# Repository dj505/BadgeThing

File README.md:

# Untitled
A small homebrew dev board, previously known as BadgeThing

# What is it?
Untitled is a software-focused development board, and an excuse for me to learn a bit more about some specific hardware I'd like to incorporate into future projects. The main focus is the integrated SSD1306 OLED display, which I've used in earlier projects as a separate module. This time around, I wanted to adapt the circuit into the project itself to make the whole thing more cohesive.

I figured since it was going to have a screen, I needed to be able to use the screen for something, so I included hardware I was already familiar with to interface with. There's the RP2040 I've used in other previous projects, and I've played with the ESP8266 before in the context of Arduino-like programming, so I thought I would try integrating that into this design so I could play with the AT firmware a little. I've used WS2812B LEDs a ton and thought they'd make a good set of indicators. And, since I wanted this to be versatile, it features some screw holes as well as slits along either side to mount using a wrist strap or some type of band to attach to other things without screws. It could even be wearable!

Oh, and it's called "Untitled" because I couldn't think of a witty name for this one. I originally wanted to call it the "no name development board with rp2040 and esp8266" with a logo and black/yellow colour scheme that parody the Canadian "no name" brand, but JLC doesn't offer black silkscreen on yellow solder mask, so I had to change it up.

# Features
- Built-in SSD1306 128*64 OLED display driven over SPI
- Raspberry Pi RP2040
- ESP-12 module for WiFi
  - Compatible with ESP-12E, ESP-12F, and ESP-12S
- Piezo buzzer pins (though they can be repurposed for other parts that use 1 GPIO)
- Row of 4 addressable RGB LEDs
- 5 buttons for input and/or navigation
- Extra GPIO broken out, with access to additional SPI/UART/I2C busses if needed
- Wristband/wrist strap slots and mounting holes

# Custom SSD1306 footprint
I couldn't find an easy-to-place foorptint for the 30-pin SSD1306 display, so this project includes a custom KICAD footprint for the typical 12mm length/7mm pin pitch ribbon cable variant you can find for cheap on AliExpress. There are 4 variants, two meant for mounting the screen on the front of the board, and two for mounting it on the back. Both placements have variants including and excluding a cutout in the Edge.Cuts layer for the ribbon cable to pass through. **You are free to use these footprints in any project you want! I just ask that credit is provided.**

There is also a custom symbol in the schematic for the display, based off of Adafruit's schematic. I can't guarantee all the pins are labelled correctly. I have tested it, and it does work, but you should research and double check the correct pinouts for your own project.

If you end up using either of these, and found them useful, please consider sending a small tip my way!  

# Parts
The majority of the parts are clearly labelled in the schematic and/or come with LCSC part numbers available through JLC. Not all of them are basic parts, unfortunately, but I used as many as I possibly could. You're also free to order part like the ESP-12 module separately and solder it yourself to save on assembly costs. However, it's important to keep in mind the following:
- The OLED diplay is made with a **0.7mm pin pitch in mind.** Some of the displays available have a 0.5mm pin pitch and will not fit.
- The display's ribbon cable should be **no longer than ~12mm** otherwise it will not fit the footprint without extra slack.
- Every ESP-12 model should fit this footprint, however I use the ESP-12S due to it supposedly having the best antenna efficiency. The missing pins along the bottom of the footprint are OK because this design does not use them, and they only serve to provide extra mechanical strength.
- The RGB LEDs are made with WS2812B-V5 LEDs in mind specifically, as they have built-in capacitors and such that I was not able to reliably fit on the PCB. Other pin-compatible and signal-compatible LEDs will work, and there is a footprint for one large capacitor. In my testing, LEDs that don't have a built in capacitor worked fine without one, but there may be cases where this does not hold true. Check the datasheet for the LEDs you plan to use to make sure they do not require an external capacitor.

# Ordering for assembly
As this project is meant to be mainly for personal use, I won't go into extensive detail here on how to order this board for assembly. However, a pre-made gerber zip is included in the "production" directory, and the BOM/CPL files can be generated through KiCAD. I recommend using the JLCPCB export plugin to do the heavy lifting for you - the LCSC part numbers I used for most components should be included in the schematic. Feel free to poke me with questions over Discord! You can reach me @dj505.

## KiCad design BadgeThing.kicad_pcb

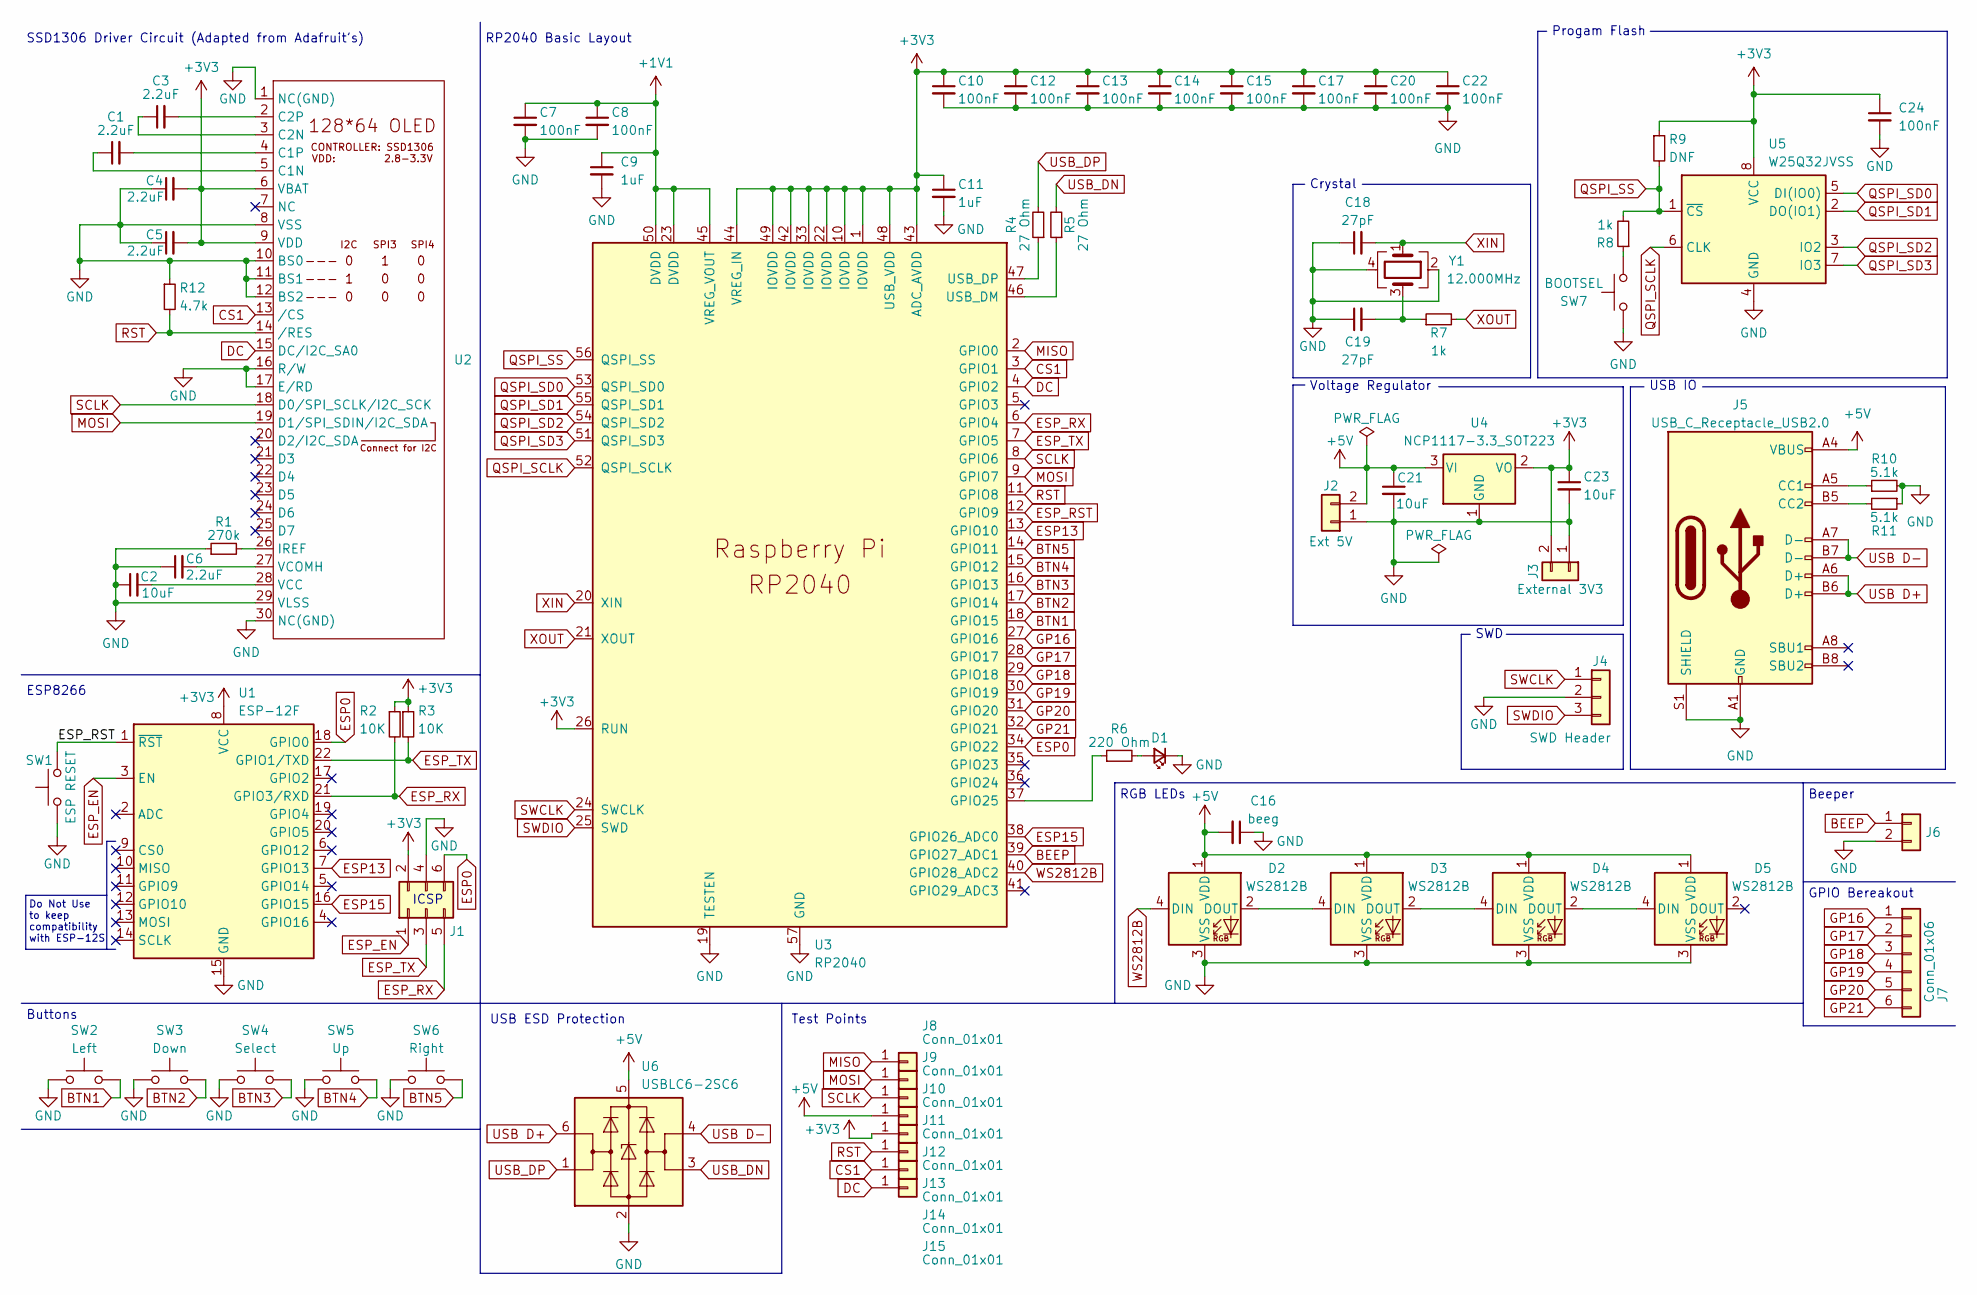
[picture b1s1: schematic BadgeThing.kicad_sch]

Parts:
C1, C3, C4, C5, C6: 2.2uF; C_0402_1005Metric_Pad0.74x0.62mm_HandSolder; LCSC C12530
C2, C21, C23: 10uF; C_0402_1005Metric_Pad0.74x0.62mm_HandSolder; LCSC C15525
C7, C8, C10, C12, C13, C14, C15, C17, C20, C22, C24: 100nF; C_0402_1005Metric_Pad0.74x0.62mm_HandSolder; LCSC C1525
C9, C11: 1uF; C_0402_1005Metric_Pad0.74x0.62mm_HandSolder; LCSC C52923
C16: beeg; C_0402_1005Metric_Pad0.74x0.62mm_HandSolder; LCSC C12530
C18, C19: 27pF; C_0402_1005Metric_Pad0.74x0.62mm_HandSolder; LCSC C1557
D1: DNF; LED_0805_2012Metric_Pad1.15x1.40mm_HandSolder; LCSC C2297
D2, D3, D4, D5: WS2812B; LED_WS2812B_PLCC4_5.0x5.0mm_P3.2mm; LCSC C2761795
J1: PinHeader_2x03_P2.54mm_Vertical
J2: Ext 5V; PinHeader_1x02_P2.54mm_Vertical
J3: External 3V3; PinHeader_1x02_P2.54mm_Vertical
J4: SWD Header; PinHeader_1x03_P1.27mm_Vertical
J5: USB_C_Receptacle_USB2.0; USB_C_Receptacle_G-Switch_GT-USB-7010ASV; LCSC C2988369
J6: Connector_Generic_Conn_01x02; PinHeader_1x02_P2.54mm_Vertical
J7: Conn_01x06; PinHeader_1x06_P2.00mm_Vertical
J8, J9, J10, J11, J12, J13, J14, J15: Conn_01x01; PinHeader_1x01_P2.00mm_Vertical
R1: 270k; R_0402_1005Metric_Pad0.72x0.64mm_HandSolder; LCSC C25770
R2, R3: 10K; R_0402_1005Metric_Pad0.72x0.64mm_HandSolder; LCSC C25744
R4, R5: 27 Ohm; R_0402_1005Metric_Pad0.72x0.64mm_HandSolder; LCSC C2909343
R6: 220 Ohm; R_0402_1005Metric_Pad0.72x0.64mm_HandSolder; LCSC C25091
R7, R8: 1k; R_0402_1005Metric_Pad0.72x0.64mm_HandSolder; LCSC C11702
R9: DNF; R_0402_1005Metric_Pad0.72x0.64mm_HandSolder; LCSC C25744
R10, R11: 5.1k; R_0402_1005Metric_Pad0.72x0.64mm_HandSolder; LCSC C25905
R12: 4.7k; R_0402_1005Metric_Pad0.72x0.64mm_HandSolder; LCSC C25900
SW1: ESP RESET; SW_Push_1P1T_XKB_TS-1187A; LCSC C318884
SW2: Left; SW_Push_1P1T_NO_6x6mm_H9.5mm
SW3: Down; SW_Push_1P1T_NO_6x6mm_H9.5mm
SW4: Select; SW_Push_1P1T_NO_6x6mm_H9.5mm
SW5: Up; SW_Push_1P1T_NO_6x6mm_H9.5mm
SW6: Right; SW_Push_1P1T_NO_6x6mm_H9.5mm
SW7: BOOTSEL; SW_Push_1P1T_XKB_TS-1187A; LCSC C318884
U1: ESP-12F; ESP-12E; LCSC C82898
U2: SSD1306 0.5mm Pitch
U3: RP2040; RP2040-QFN-56; LCSC C2040
U4: NCP1117-3.3_SOT223; SOT-223-3_TabPin2; LCSC C146799
U5: W25Q32JVSS; SOIC-8_5.23x5.23mm_P1.27mm; LCSC C82344
U6: USBLC6-2SC6; SOT-23-6; LCSC C2687116
Y1: 12.000MHz; Crystal_SMD_3225-4Pin_3.2x2.5mm; LCSC C9002

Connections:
+1V1: C7.1, C8.1, C9.1, U3.23 (DVDD), U3.45 (VREG_VOUT), U3.50 (DVDD)
+3V3: C4.2, C5.2, C10.1, C11.1, C12.1, C13.1, C14.1, C15.1, C17.1, C20.1, C22.1, C23.1, C24.1, J1.2, J3.2, J12.1, R2.1, R3.1, R9.1, U1.8 (VCC), U2.6 (VBAT), U2.9 (VDD), U3.1 (IOVDD), U3.10 (IOVDD), U3.22 (IOVDD), U3.26 (RUN), U3.33 (IOVDD), U3.42 (IOVDD), U3.43 (ADC_AVDD), U3.44 (VREG_IN), U3.48 (USB_VDD), U3.49 (IOVDD), U4.2 (VO), U5.8 (VCC)
+5V: C16.2, C21.1, D2.1 (VDD), D3.1 (VDD), D4.1 (VDD), D5.1 (VDD), J2.2, J5.A4 (VBUS), J5.A9 (VBUS), J5.B4 (VBUS), J5.B9 (VBUS), J11.1, U4.3 (VI), U6.5 (VBUS)
BEEP: J6.1, U3.39 (GPIO27_ADC1)
BTN1: SW2.2, U3.18 (GPIO15)
BTN2: SW3.2, U3.17 (GPIO14)
BTN3: SW4.2, U3.16 (GPIO13)
BTN4: SW5.2, U3.15 (GPIO12)
BTN5: SW6.2, U3.14 (GPIO11)
CS1: J14.1, U2.13 (/CS), U3.3 (GPIO1)
DC: J15.1, U2.15 (DC/I2C_SA0), U3.4 (GPIO2)
ESP0: J1.6, U1.18 (GPIO0), U3.34 (GPIO22)
ESP13: U1.7 (GPIO13), U3.13 (GPIO10)
ESP15: U1.16 (GPIO15), U3.38 (GPIO26_ADC0)
ESP_EN: J1.1, U1.3 (EN)
ESP_RST: SW1.2, U1.1 (~RST), U3.12 (GPIO9)
ESP_RX: J1.5, R2.2, U1.21 (GPIO3/RXD), U3.6 (GPIO4)
ESP_TX: J1.3, R3.2, U1.22 (GPIO1/TXD), U3.7 (GPIO5)
GND: C2.1, C4.1, C5.1, C6.1, C7.2, C8.2, C9.2, C10.2, C11.2, C12.2, C13.2, C14.2, C15.2, C16.1, C17.2, C18.1, C19.1, C20.2, C21.2, C22.2, C23.2, C24.2, D1.1 (K), D2.3 (VSS), D3.3 (VSS), D4.3 (VSS), D5.3 (VSS), J1.4, J2.1, J3.1, J4.2, J5.A1 (GND), J5.A12 (GND), J5.B1 (GND), J5.B12 (GND), J5.S1 (SHIELD), J6.2, R1.1, R10.2, R11.1, R12.1, SW1.1, SW2.1, SW3.1, SW4.1, SW5.1, SW6.1, SW7.1, U1.15 (GND), U2.1 (NC(GND)), U2.8 (VSS), U2.10 (BS0), U2.11 (BS1), U2.12 (BS2), U2.16 (R/W), U2.17 (E/RD), U2.29 (VLSS), U2.30 (NC(GND)), U3.19 (TESTEN), U3.57 (GND), U4.1 (GND), U5.4 (GND), U6.2 (GND), Y1.2, Y1.4
GP16: J7.1, U3.27 (GPIO16)
GP17: J7.2, U3.28 (GPIO17)
GP18: J7.3, U3.29 (GPIO18)
GP19: J7.4, U3.30 (GPIO19)
GP20: J7.5, U3.31 (GPIO20)
GP21: J7.6, U3.32 (GPIO21)
MISO: J8.1, U3.2 (GPIO0)
MOSI: J9.1, U2.19 (D1/SPI_SDIN/I2C_SDA), U3.9 (GPIO7)
unnamed: C19.2, R7.1, Y1.3
unnamed: D1.2 (A), R6.2
unnamed: D2.2 (DOUT), D3.4 (DIN)
unnamed: D3.2 (DOUT), D4.4 (DIN)
unnamed: D4.2 (DOUT), D5.4 (DIN)
unnamed: J5.A5 (CC1), R10.1
unnamed: J5.B5 (CC2), R11.2
unnamed: R8.1, SW7.2
unnamed: C1.1, U2.5 (C1N)
unnamed: C1.2, U2.4 (C1P)
unnamed: C3.1, U2.3 (C2N)
unnamed: C3.2, U2.2 (C2P)
unnamed: R1.2, U2.26 (IREF)
unnamed: C2.2, U2.28 (VCC)
unnamed: C6.2, U2.27 (VCOMH)
unnamed: R6.1, U3.37 (GPIO25)
unnamed: R5.1, U3.46 (USB_DM)
unnamed: R4.1, U3.47 (USB_DP)
QSPI_SCLK: U3.52 (QSPI_SCLK), U5.6 (CLK)
QSPI_SD0: U3.53 (QSPI_SD0), U5.5 (DI(IO0))
QSPI_SD1: U3.55 (QSPI_SD1), U5.2 (DO(IO1))
QSPI_SD2: U3.54 (QSPI_SD2), U5.3 (IO2)
QSPI_SD3: U3.51 (QSPI_SD3), U5.7 (IO3)
QSPI_SS: R8.2, R9.2, U3.56 (QSPI_SS), U5.1 (~CS)
RST: J13.1, R12.2, U2.14 (/RES), U3.11 (GPIO8)
SCLK: J10.1, U2.18 (D0/SPI_SCLK/I2C_SCK), U3.8 (GPIO6)
SWCLK: J4.1, U3.24 (SWCLK)
SWDIO: J4.3, U3.25 (SWD)
USB D+: J5.A6 (D+), J5.B6 (D+), U6.6 (I/O1)
USB D-: J5.A7 (D-), J5.B7 (D-), U6.4 (I/O2)
USB_DN: R5.2, U6.3 (I/O2)
USB_DP: R4.2, U6.1 (I/O1)
WS2812B: D2.4 (DIN), U3.40 (GPIO28_ADC2)
XIN: C18.2, U3.20 (XIN), Y1.1
XOUT: R7.2, U3.21 (XOUT)

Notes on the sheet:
Buttons
USB ESD Protection
RP2040 Basic Layout
SWD
SSD1306 Driver Circuit (Adapted from Adafruit's)
Do Not Use to keep compatibility with ESP-12S
Progam Flash
ESP8266
Beeper
ICSP
Crystal
RGB LEDs
USB IO
GPIO Bereakout
Test Points
Voltage Regulator

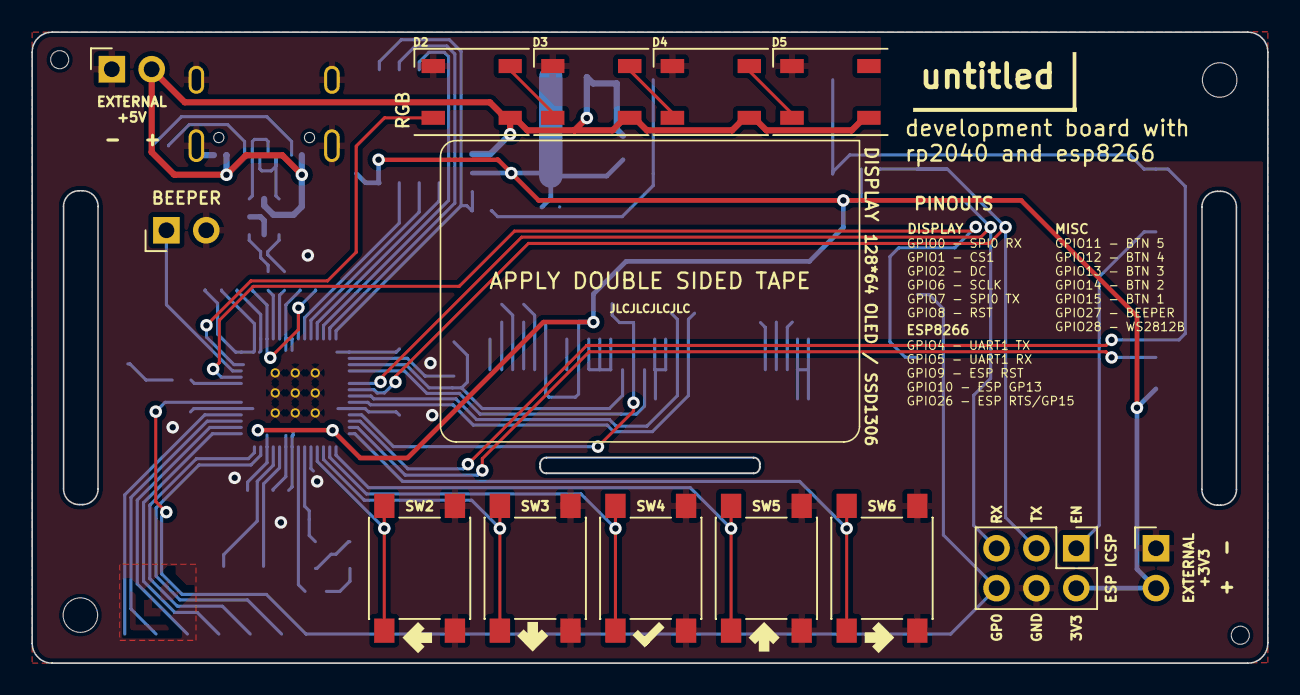
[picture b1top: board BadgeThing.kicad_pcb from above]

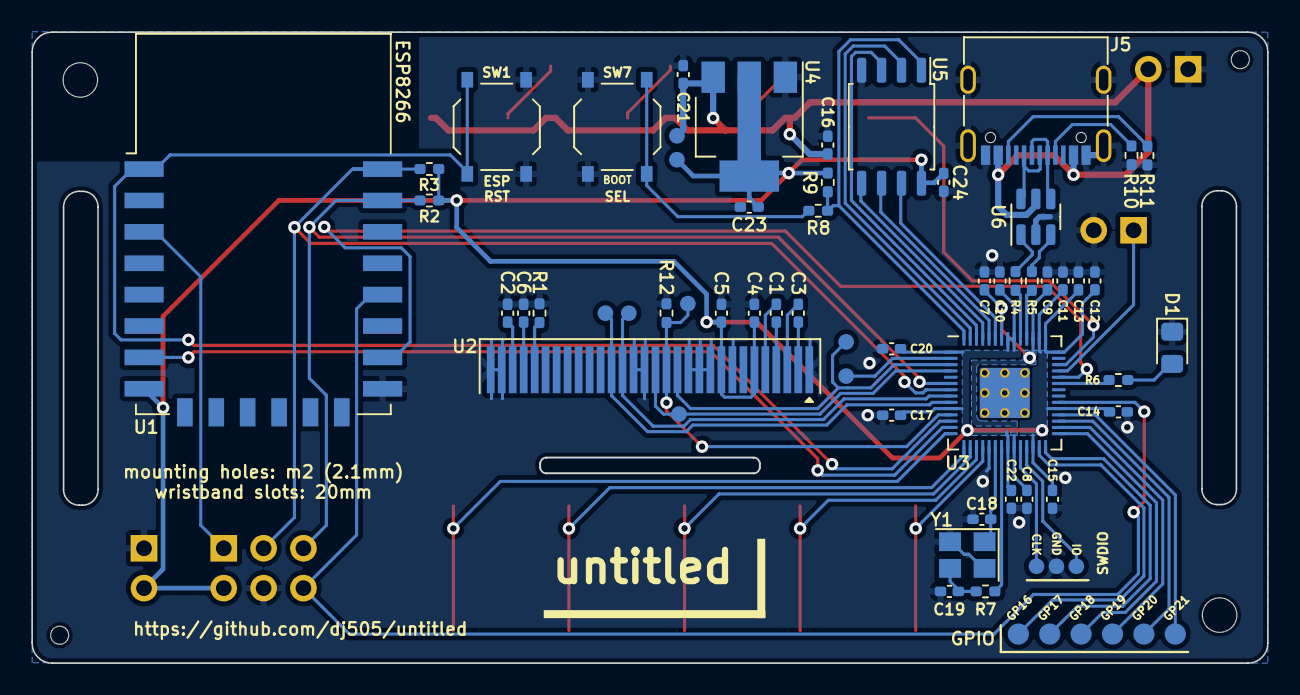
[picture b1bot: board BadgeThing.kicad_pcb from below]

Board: 2 copper layers, 78.7 x 40.2 mm, 70 parts (56 on the bottom side), 62 nets.

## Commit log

2024-01-09 Initial schematic
2024-01-12 RP2040/OLED circuits, basic component placement
2024-01-12 Schematic change
2024-01-12 more routing + layout
2024-01-12 Completed initial routing
2024-01-12 small tweaks, visual changes, added missing traces
2024-01-13 Layout tweaks + JLC part numbers
2024-01-14 Final board layout, up to first production order
2024-01-14 3V3 input + small tweaks
2024-01-15 Align 3V3 input with ESP header at 2.54mm pitch
2024-01-24 Begin re-routing, updated ssd1306 pinout (not backwards anymore)
2024-01-25 Continue routing
2024-01-26 huge routing optimizations and extra features
2024-01-26 Final routing
2024-01-27 Updated SSD1306 30-pin footprints
2024-01-27 Finishing touches
2024-01-28 finishing finishing touches
2024-01-28 Update 3D models
2024-01-28 Final finishing touches (fix silly mistakes)
2024-01-28 tweaked 1v1 plane
2024-01-29 Real final finishing touches
2024-01-29 consider adding an SD card slot
2024-01-29 Actual final real finishing touches (+test pads)
2024-02-05 Remove microsd submodule, unneeded
2024-02-12 Fix SPI wiring, add ESP RTS pin, add prod files
